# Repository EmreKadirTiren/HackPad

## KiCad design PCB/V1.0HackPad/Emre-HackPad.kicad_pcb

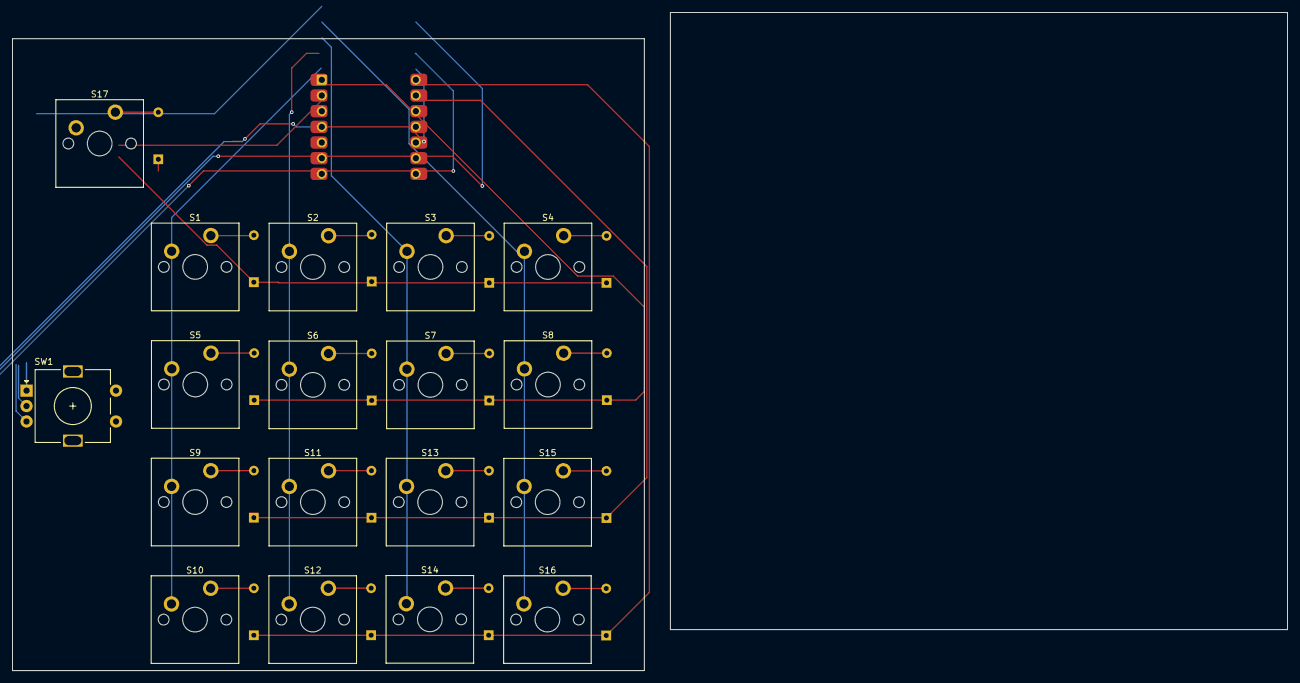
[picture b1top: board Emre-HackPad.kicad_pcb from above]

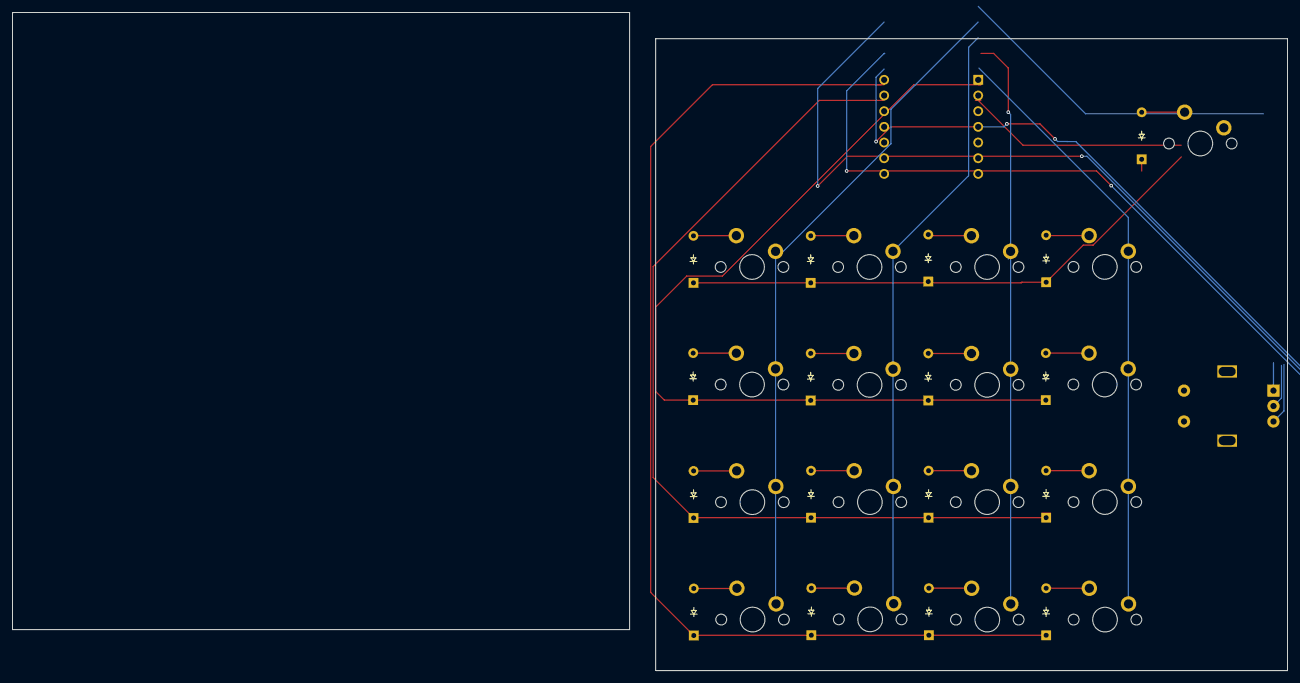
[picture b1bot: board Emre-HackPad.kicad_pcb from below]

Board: 2 copper layers, 102.4 x 102.4 mm, 36 parts (17 on the bottom side), 29 nets.

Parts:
D1, D2, D3, D4, D5, D6, D7, D8, D9, D10, D11, D12, D13, D14, D15, D16, D17: Diode; Diode_DO-35
S1, S2, S3, S4, S5, S6, S7, S8, S9, S10, S11, S12, S13, S14, S15, S16, S17: Keyswitch; MX_PCB_1.00u
SW1: RotaryEncoder; RotaryEncoder_Alps_EC11E-Switch_Vertical_H20mm
U1: Seeed Studio XIAO SAMD21; Seeed_XIAO_RP2040

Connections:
Column0: S1.1, S5.1, S9.1, S10.1, U1.5 (PA8_A4_D4_SDA)
Column1: S2.1, S6.1, S11.1, S12.1, U1.4 (PA11_A3_D3)
Column2: S3.1, S7.1, S13.1, S14.1, U1.3 (PA10_A2_D2)
Column3: S4.1, S8.1, S15.1, S16.1, U1.2 (PA4_A1_D1)
Column4: S17.1, U1.1 (PA02_A0_D0)
GND: SW1.C, U1.13 (GND)
unnamed: D1.2 (A), S1.2
unnamed: D2.2 (A), S2.2
unnamed: D3.2 (A), S3.2
unnamed: D4.2 (A), S4.2
unnamed: D5.2 (A), S5.2
unnamed: D6.2 (A), S6.2
unnamed: D7.2 (A), S7.2
unnamed: D8.2 (A), S8.2
unnamed: D9.2 (A), S9.2
unnamed: D10.2 (A), S10.2
unnamed: D11.2 (A), S11.2
unnamed: D12.2 (A), S12.2
unnamed: D13.2 (A), S13.2
unnamed: D14.2 (A), S14.2
unnamed: D15.2 (A), S15.2
unnamed: D16.2 (A), S16.2
unnamed: D17.2 (A), S17.2
unnamed: SW1.B, U1.10 (PA5_A9_D9_MISO)
unnamed: SW1.A, U1.11 (PA6_A10_D10_MOSI)
Row0: D1.1 (K), D2.1 (K), D3.1 (K), D4.1 (K), D17.1 (K), U1.7 (PB08_A6_D6_TX)
Row1: D5.1 (K), D6.1 (K), D7.1 (K), D8.1 (K), U1.6 (PA9_A5_D5_SCL)
Row2: D9.1 (K), D11.1 (K), D13.1 (K), D15.1 (K), U1.8 (PB09_A7_D7_RX)
Row3: D10.1 (K), D12.1 (K), D14.1 (K), D16.1 (K), U1.9 (PA7_A8_D8_SCK)

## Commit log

2024-10-05 HackPad v1.0
2024-10-05 Update V1 and Added V2
2024-10-06 Added V3 HackPad
    This version has 4x4 switches and on the left there is a rotary encoder
2024-10-13 Auto stash before merge of "main" and "origin/main"
2024-10-14 Added some things and moved some things around
    Updated some 3d models and moved a thew things around. :) But now I am finally done!!
2024-12-17 Case V3 Update + HackPadV4 UPdate
2024-12-17 Case Plate V4 Update
    Didn't design my plate good enough so my encoder could not fit in the plate.
